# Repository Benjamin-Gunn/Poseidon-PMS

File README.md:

# Poseidon-PMS
Power Management System for Poseidon.

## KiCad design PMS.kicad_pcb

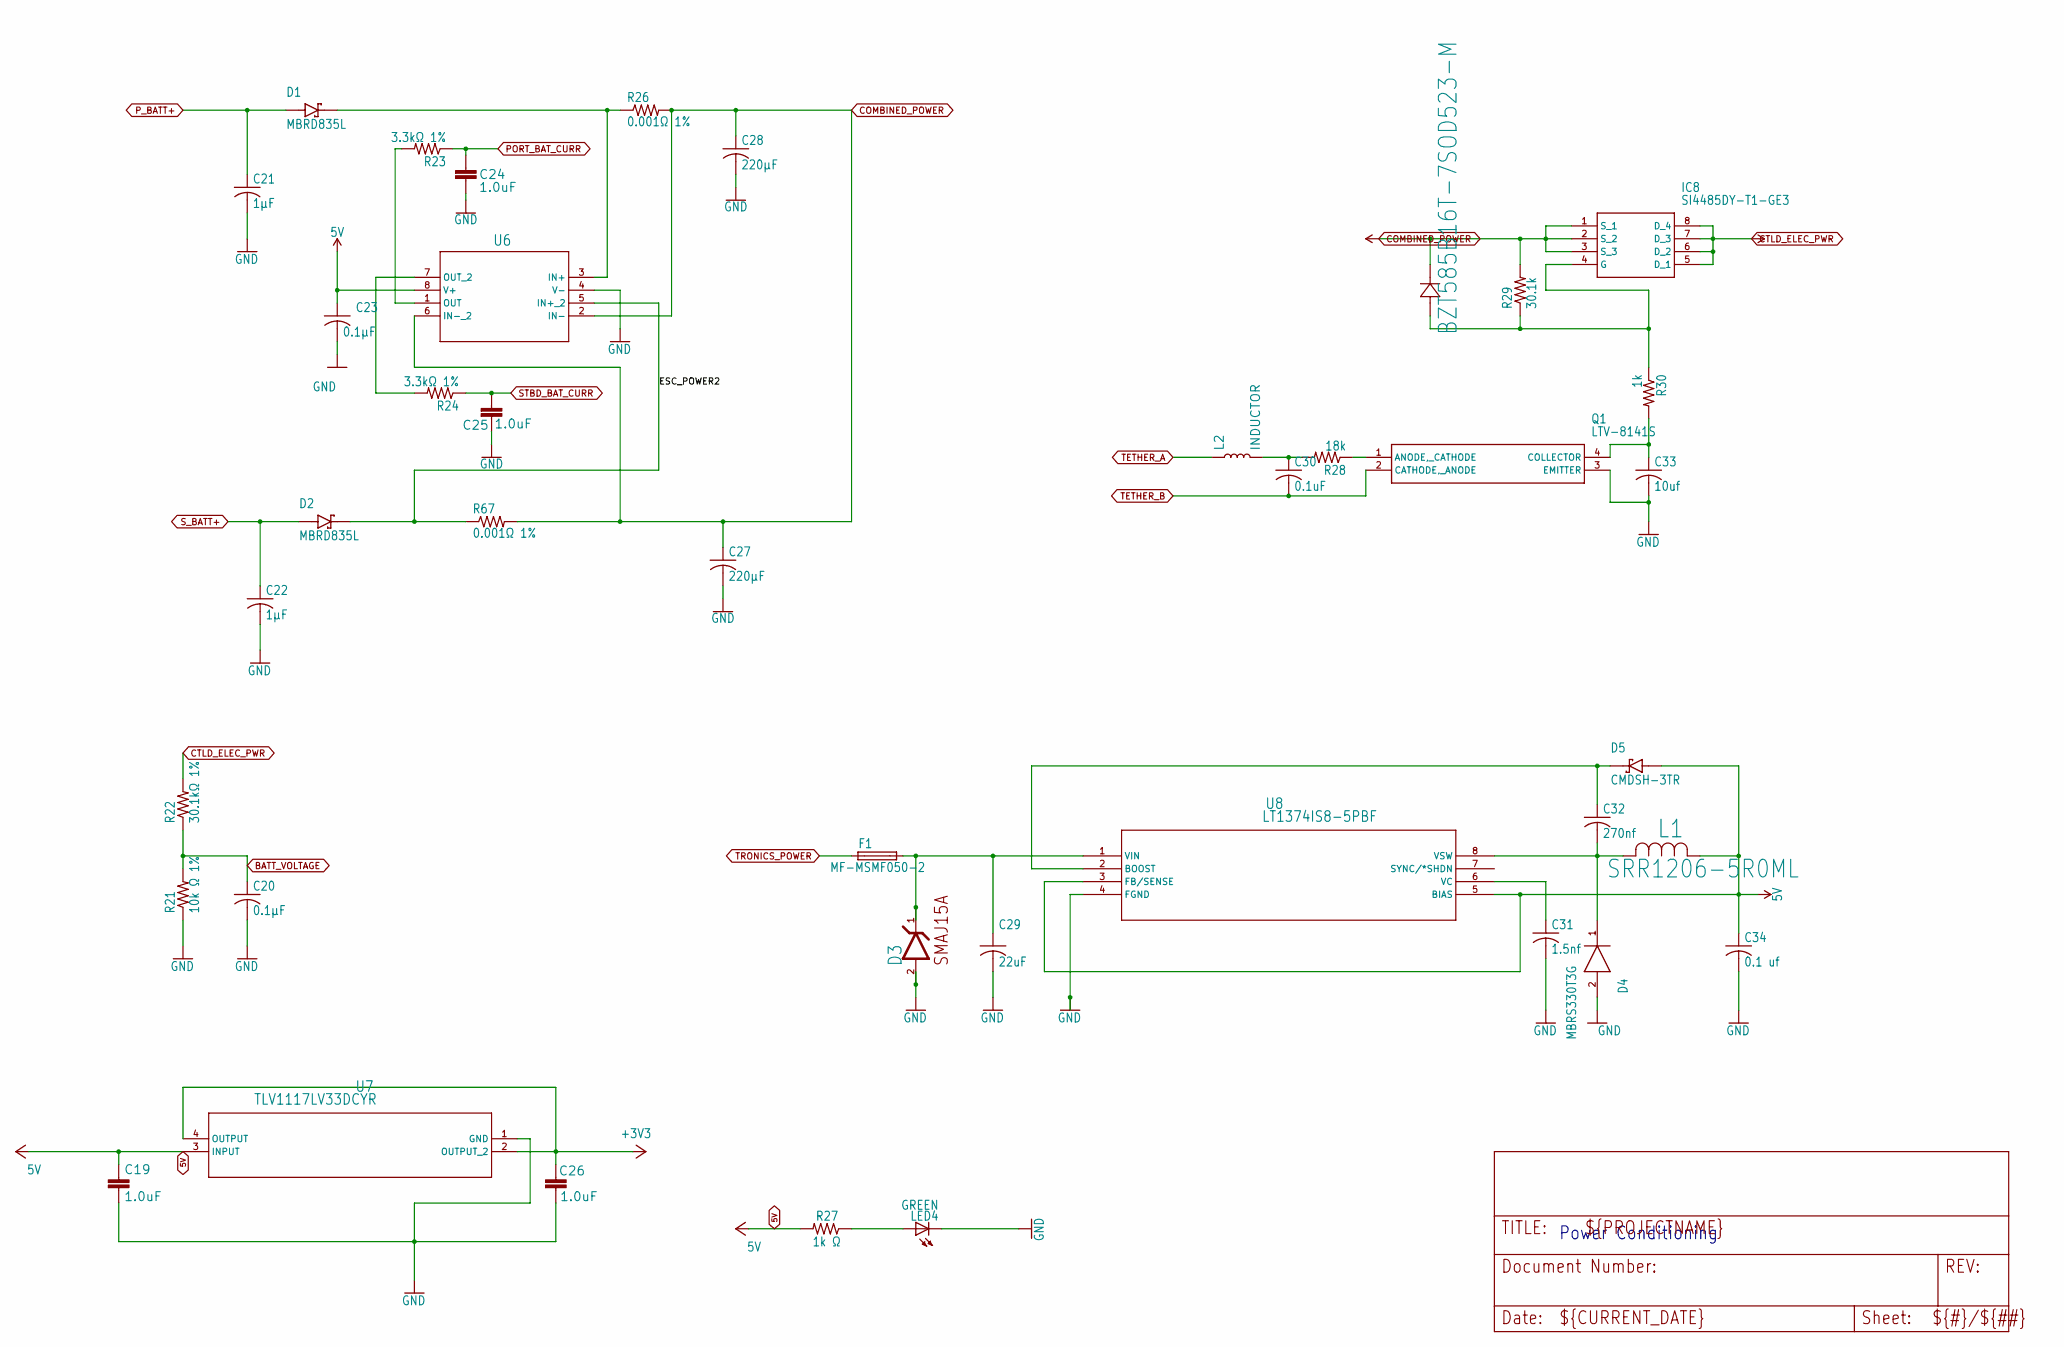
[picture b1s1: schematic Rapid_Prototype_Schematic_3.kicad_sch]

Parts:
C19, C24, C25, C26: 1.0uF; C_0805_2012Metric
C20, C23: 0.1µF; C_0805_2012Metric
C21, C22: 1µF; C_0805_2012Metric
C27, C28: 220µF; C_1206_3216Metric
C29: 22uF; C_0805_2012Metric
C30: 0.1uF; C_0805_2012Metric
C31: 1.5nf; C_0805_2012Metric
C32: 270nf; C_0805_2012Metric
C33: 10uf; C_0805_2012Metric
C34: 0.1 uf; C_0805_2012Metric
CR1: BZT585B16T-7SOD523-M; D_SOD-323_HandSoldering
D1, D2: MBRD835L; TO-252-3_TabPin2_1
D3: BOURNS-INC.---SMAJ15A_BOURNS_INC._SMAJ15ABOURNS_I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; D_SMA_Handsoldering
D4: MBRS330T3G; D_SMC_Handsoldering
D5: CMDSH-3TR; D_SOD-323_HandSoldering
F1: MF-MSMF050-2; Fuse_1812_4532Metric_Pad1.30x3.40mm_HandSolder
IC8: SI4485DY-T1-GE3; SOIC-8_3.9x4.9mm_P1.27mm
L1: SRR1206-5R0ML; IND_BOURNS_SRR1240
L2: INDUCTOR; SRP1770TA-3R3M_BRN
LED4: GREEN; LED_0805_2012Metric_Pad1.15x1.40mm_HandSolder
Q1: LTV-8141S; LTV8141STA1
R21: 10k Ω 1%; R_0805_2012Metric_Pad1.20x1.40mm_HandSolder
R22: 30.1kΩ 1%; R_0805_2012Metric_Pad1.20x1.40mm_HandSolder
R23, R24: 3.3kΩ 1%; R_0805_2012Metric_Pad1.20x1.40mm_HandSolder
R26, R67: 0.001Ω 1%; R_0805_2012Metric_Pad1.20x1.40mm_HandSolder
R27: 1k Ω; R_0805_2012Metric_Pad1.20x1.40mm_HandSolder
R28: 18k; R_0805_2012Metric_Pad1.20x1.40mm_HandSolder
R29: 30.1k; R_0805_2012Metric_Pad1.20x1.40mm_HandSolder
R30: 1k; R_0805_2012Metric_Pad1.20x1.40mm_HandSolder
U6: LM2904ITPX/NOPB; SOIC-8_3.9x4.9mm_P1.27mm
U7: TLV1117LV33DCYR; SOT-223
U8: LT1374IS8-5PBF; SOIC-8_3.9x4.9mm_P1.27mm

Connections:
5V: C19.1, C23.1, C34.1, D5.2 (A), L1.1, R27.2, U6.8 (V+), U7.3 (INPUT), U8.3 (FB/SENSE), U8.5 (BIAS); also elsewhere on the board
+3V3: C26.1, U7.2 (OUTPUT_2), U7.4 (OUTPUT); also elsewhere on the board
/Rapid_Prototype_Schematic_3/ESC_POWER2: D2.2 (K), R67.1, U6.5 (IN+_2)
BATT_VOLTAGE: C20.1, R21.2, R22.1; also elsewhere on the board
COMBINED_POWER: C27.1, C28.1, CR1.1, IC8.1 (S_1), IC8.2 (S_2), IC8.3 (S_3), R26.2, R29.2, R67.2, U6.2 (IN-), U6.6 (IN-_2); also elsewhere on the board
CTLD_ELEC_PWR: IC8.5 (D_1), IC8.6 (D_2), IC8.7 (D_3), IC8.8 (D_4), R22.2; also elsewhere on the board
GND: C19.2, C20.2, C21.2, C22.2, C23.2, C24.2, C25.2, C26.2, C27.2, C28.2, C29.2, C31.2, C33.2, C34.2, D3.2 (ANODE), D4.2 (A), LED4.1 (C), Q1.3 (EMITTER), R21.1, U6.4 (V-), U7.1 (GND), U8.4 (FGND); also elsewhere on the board
unnamed: C30.1, L2.2, R28.2
unnamed: D1.2 (K), R26.1, U6.3 (IN+)
unnamed: C29.1, D3.1 (CATHODE), F1.2, U8.1 (VIN)
unnamed: C32.2, D4.1 (K), L1.2, U8.8 (VSW)
unnamed: C32.1, D5.1 (C), U8.2 (BOOST)
unnamed: CR1.2, IC8.4 (G), R29.1, R30.1
unnamed: LED4.2 (A), R27.1
unnamed: Q1.1 (ANODE,_CATHODE), R28.1
unnamed: C33.1, Q1.4 (COLLECTOR), R30.2
unnamed: R23.2, U6.1 (OUT)
unnamed: R24.2, U6.7 (OUT_2)
unnamed: C31.1, U8.6 (VC)
PORT_BAT_CURR: C24.1, R23.1; also elsewhere on the board
P_BATT+: C21.1, D1.1 (A); also elsewhere on the board
STBD_BAT_CURR: C25.1, R24.1; also elsewhere on the board
S_BATT+: C22.1, D2.1 (A); also elsewhere on the board
TETHER_A: L2.1; also elsewhere on the board
TETHER_B: C30.2, Q1.2 (CATHODE,_ANODE); also elsewhere on the board
TRONICS_POWER: F1.1; also elsewhere on the board

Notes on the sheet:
Power Conditioning

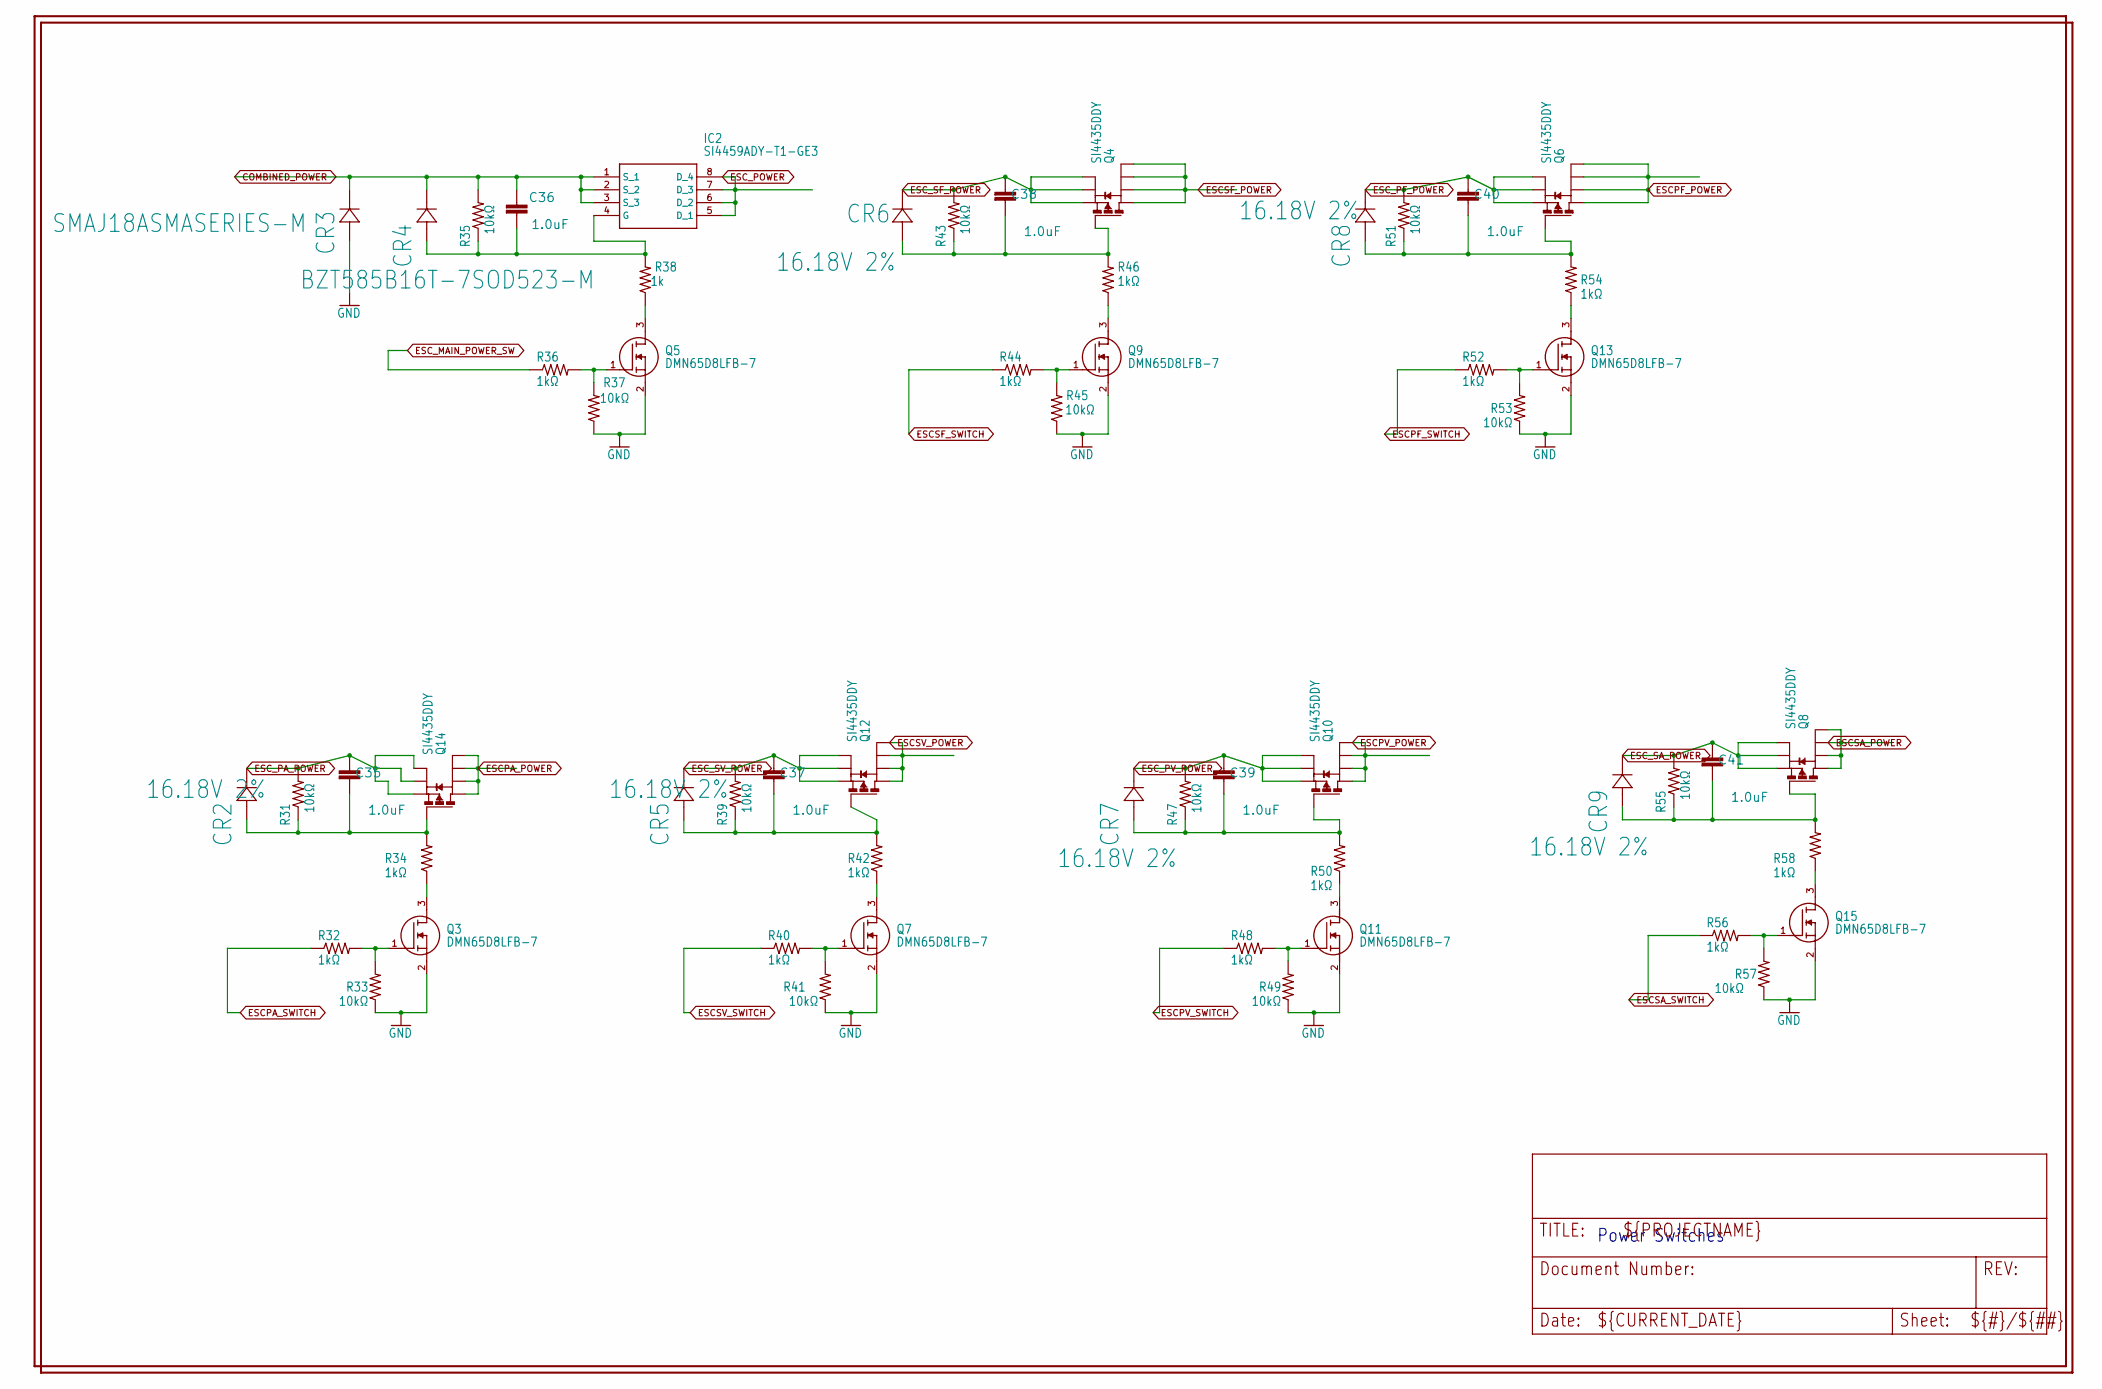
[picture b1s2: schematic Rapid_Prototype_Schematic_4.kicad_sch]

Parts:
C35, C36, C37, C38, C39, C40, C41: 1.0uF; C_0805_2012Metric
CR2, CR5, CR6, CR7, CR8, CR9: 16.18V 2%; D_SOD-323_HandSoldering
CR3: SMAJ18ASMASERIES-M; D_SMA_Handsoldering
CR4: BZT585B16T-7SOD523-M; D_SOD-323_HandSoldering
IC2: SI4459ADY-T1-GE3; SOIC-8_3.9x4.9mm_P1.27mm
Q3, Q5, Q7, Q9, Q11, Q13, Q15: DMN65D8LFB-7; SOT-23-3
Q4, Q6, Q8, Q10, Q12, Q14: SI4435DDY; SOIC-8_3.9x4.9mm_P1.27mm
R31, R33, R35, R37, R39, R41, R43, R45, R47, R49, R51, R53, R55, R57: 10kΩ; R_0805_2012Metric_Pad1.20x1.40mm_HandSolder
R32, R34, R36, R40, R42, R44, R46, R48, R50, R52, R54, R56, R58: 1kΩ; R_0805_2012Metric_Pad1.20x1.40mm_HandSolder
R38: 1k; R_0805_2012Metric_Pad1.20x1.40mm_HandSolder

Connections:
COMBINED_POWER: C36.1, CR3.1, CR4.1, IC2.1 (S_1), IC2.2 (S_2), IC2.3 (S_3), R35.2; also elsewhere on the board
ESCPA_POWER: Q14.5 (D@1), Q14.6 (D@2), Q14.7 (D@3), Q14.8 (D@4); also elsewhere on the board
ESCPA_SWITCH: R32.1; also elsewhere on the board
ESCPF_POWER: Q6.5 (D@1), Q6.6 (D@2), Q6.7 (D@3), Q6.8 (D@4); also elsewhere on the board
ESCPF_SWITCH: R52.1; also elsewhere on the board
ESCPV_POWER: Q10.5 (D@1), Q10.6 (D@2), Q10.7 (D@3), Q10.8 (D@4); also elsewhere on the board
ESCPV_SWITCH: R48.1; also elsewhere on the board
ESCSA_POWER: Q8.5 (D@1), Q8.6 (D@2), Q8.7 (D@3), Q8.8 (D@4); also elsewhere on the board
ESCSA_SWITCH: R56.1; also elsewhere on the board
ESCSF_POWER: Q4.5 (D@1), Q4.6 (D@2), Q4.7 (D@3), Q4.8 (D@4); also elsewhere on the board
ESCSF_SWITCH: R44.1; also elsewhere on the board
ESCSV_POWER: Q12.5 (D@1), Q12.6 (D@2), Q12.7 (D@3), Q12.8 (D@4); also elsewhere on the board
ESCSV_SWITCH: R40.1; also elsewhere on the board
ESC_MAIN_POWER_SW: R36.1; also elsewhere on the board
ESC_PA_POWER: C35.1, CR2.1, Q14.1 (S@1), Q14.2 (S@2), Q14.3 (S@3), R31.2; also elsewhere on the board
ESC_PF_POWER: C40.1, CR8.1, Q6.1 (S@1), Q6.2 (S@2), Q6.3 (S@3), R51.2; also elsewhere on the board
ESC_POWER: IC2.5 (D_1), IC2.6 (D_2), IC2.7 (D_3), IC2.8 (D_4); also elsewhere on the board
ESC_PV_POWER: C39.1, CR7.1, Q10.1 (S@1), Q10.2 (S@2), Q10.3 (S@3), R47.2; also elsewhere on the board
ESC_SA_POWER: C41.1, CR9.1, Q8.1 (S@1), Q8.2 (S@2), Q8.3 (S@3), R55.2; also elsewhere on the board
ESC_SF_POWER: C38.1, CR6.1, Q4.1 (S@1), Q4.2 (S@2), Q4.3 (S@3), R43.2; also elsewhere on the board
ESC_SV_POWER: C37.1, CR5.1, Q12.1 (S@1), Q12.2 (S@2), Q12.3 (S@3), R39.2; also elsewhere on the board
GND: CR3.2, Q3.2 (S), Q5.2 (S), Q7.2 (S), Q9.2 (S), Q11.2 (S), Q13.2 (S), Q15.2 (S), R33.1, R37.1, R41.1, R45.1, R49.1, R53.1, R57.1; also elsewhere on the board
unnamed: C36.2, CR4.2, IC2.4 (G), R35.1, R38.2
unnamed: Q3.3 (D), R34.1
unnamed: Q3.1 (G), R32.2, R33.2
unnamed: C38.2, CR6.2, Q4.4 (G), R43.1, R46.2
unnamed: Q5.3 (D), R38.1
unnamed: Q5.1 (G), R36.2, R37.2
unnamed: C40.2, CR8.2, Q6.4 (G), R51.1, R54.2
unnamed: Q7.3 (D), R42.1
unnamed: Q7.1 (G), R40.2, R41.2
unnamed: C41.2, CR9.2, Q8.4 (G), R55.1, R58.2
unnamed: Q9.3 (D), R46.1
unnamed: Q9.1 (G), R44.2, R45.2
unnamed: C39.2, CR7.2, Q10.4 (G), R47.1, R50.2
unnamed: Q11.3 (D), R50.1
unnamed: Q11.1 (G), R48.2, R49.2
unnamed: C37.2, CR5.2, Q12.4 (G), R39.1, R42.2
unnamed: Q13.3 (D), R54.1
unnamed: Q13.1 (G), R52.2, R53.2
unnamed: C35.2, CR2.2, Q14.4 (G), R31.1, R34.2
unnamed: Q15.3 (D), R58.1
unnamed: Q15.1 (G), R56.2, R57.2

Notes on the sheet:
Power Switches

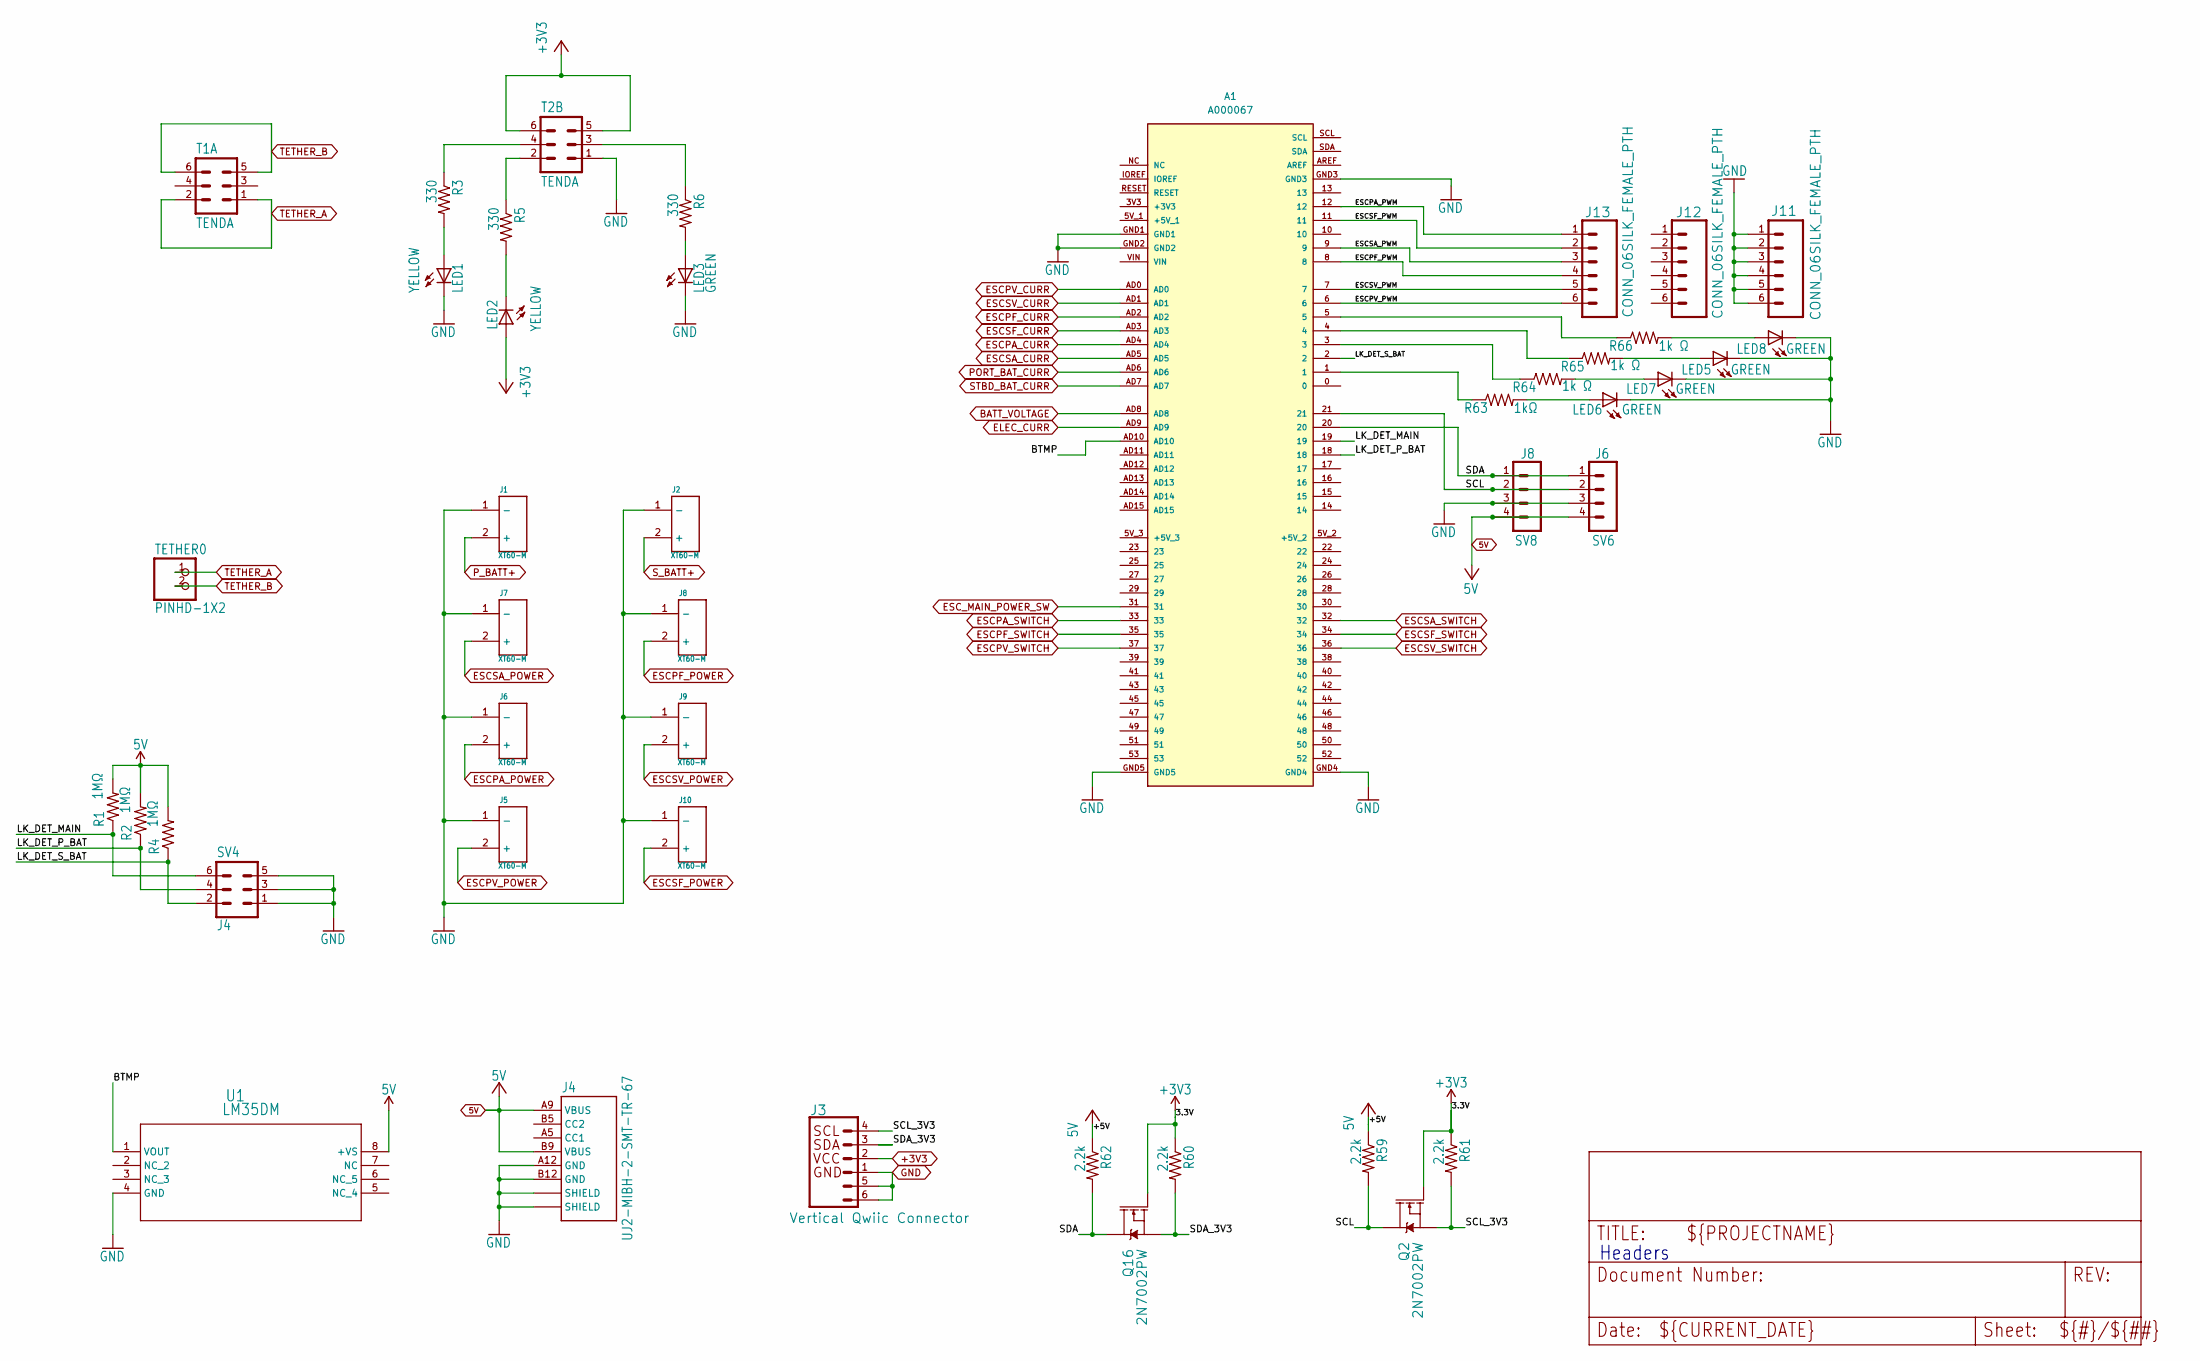
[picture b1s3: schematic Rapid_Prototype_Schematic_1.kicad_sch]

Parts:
A1: A000067; MODULE_A000067
J1, J2, J5, J6, J7, J8, J9, J10: XT60-M; AMASS_XT60-M_1x02_P7.20mm_Vertical
J3: Vertical Qwiic Connector; CONN_BM04B-SRSS-TB_SPK
J4: UJ2-MIBH-2-SMT-TR-67; GCT_USB4125-GF-A_REVA2
J11, J12, J13: CONN_06SILK_FEMALE_PTH; PinSocket_1x06_P2.54mm_Vertical
LED1, LED2: YELLOW; LED_0805_2012Metric_Pad1.15x1.40mm_HandSolder
LED3, LED5, LED6, LED7, LED8: GREEN; LED_0805_2012Metric_Pad1.15x1.40mm_HandSolder
Q2, Q16: 2N7002PW; SOT-23-3
R1, R2, R4: 1MΩ; R_0805_2012Metric_Pad1.20x1.40mm_HandSolder
R3, R5, R6: 330; R_0805_2012Metric_Pad1.20x1.40mm_HandSolder
R59, R60, R61, R62: 2.2k; R_0805_2012Metric_Pad1.20x1.40mm_HandSolder
R63: 1kΩ; R_0805_2012Metric_Pad1.20x1.40mm_HandSolder
R64, R65, R66: 1k Ω; R_0805_2012Metric_Pad1.20x1.40mm_HandSolder
SV4: J4; PinSocket_2x03_P2.54mm_Vertical
SV6: J6; PinSocket_1x04_P2.54mm_Vertical
SV8: J8; PinSocket_1x04_P2.54mm_Vertical
T1, T2: TENDA; PinSocket_2x03_P2.54mm_Vertical
TETHER0: PINHD-1X2; PinSocket_1x02_P2.54mm_Vertical
U1: LM35DM; SOIC-8_3.9x4.9mm_P1.27mm

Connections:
5V: J4.A9 (VBUS), J4.B9 (VBUS), R1.2, R2.2, R4.2, R59.1, R62.1, SV6.4, SV8.4, U1.8 (+VS); also elsewhere on the board
+3V3: J3.2, LED2.2 (A), Q2.1 (G), Q16.1 (G), R60.1, R61.1, T2.5, T2.6; also elsewhere on the board
/Rapid_Prototype_Schematic_1/BTMP: A1.AD10, U1.1 (VOUT)
/Rapid_Prototype_Schematic_1/ESCPA_PWM: A1.12, J13.1
/Rapid_Prototype_Schematic_1/ESCPF_PWM: A1.8, J13.4
/Rapid_Prototype_Schematic_1/ESCPV_PWM: A1.6, J13.6
/Rapid_Prototype_Schematic_1/ESCSA_PWM: A1.9, J13.3
/Rapid_Prototype_Schematic_1/ESCSF_PWM: A1.11, J13.2
/Rapid_Prototype_Schematic_1/ESCSV_PWM: A1.7, J13.5
/Rapid_Prototype_Schematic_1/LK_DET_MAIN: A1.19, R1.1, SV4.6
/Rapid_Prototype_Schematic_1/LK_DET_P_BAT: A1.18, R2.1, SV4.4
/Rapid_Prototype_Schematic_1/LK_DET_S_BAT: A1.2, R4.1, SV4.2
/Rapid_Prototype_Schematic_1/SCL: A1.21, Q2.3 (D), R59.2, SV6.2, SV8.2
/Rapid_Prototype_Schematic_1/SCL_3V3: J3.4, Q2.2 (S), R61.2
/Rapid_Prototype_Schematic_1/SDA: A1.20, Q16.3 (D), R62.2, SV6.1, SV8.1
/Rapid_Prototype_Schematic_1/SDA_3V3: J3.3, Q16.2 (S), R60.2
BATT_VOLTAGE: A1.AD8; also elsewhere on the board
ELEC_CURR: A1.AD9; also elsewhere on the board
ESCPA_CURR: A1.AD4; also elsewhere on the board
ESCPA_POWER: J6.2 (+); also elsewhere on the board
ESCPA_SWITCH: A1.33; also elsewhere on the board
ESCPF_CURR: A1.AD2; also elsewhere on the board
ESCPF_POWER: J8.2 (+); also elsewhere on the board
ESCPF_SWITCH: A1.35; also elsewhere on the board
ESCPV_CURR: A1.AD0; also elsewhere on the board
ESCPV_POWER: J5.2 (+); also elsewhere on the board
ESCPV_SWITCH: A1.37; also elsewhere on the board
ESCSA_CURR: A1.AD5; also elsewhere on the board
ESCSA_POWER: J7.2 (+); also elsewhere on the board
ESCSA_SWITCH: A1.32; also elsewhere on the board
ESCSF_CURR: A1.AD3; also elsewhere on the board
ESCSF_POWER: J10.2 (+); also elsewhere on the board
ESCSF_SWITCH: A1.34; also elsewhere on the board
ESCSV_CURR: A1.AD1; also elsewhere on the board
ESCSV_POWER: J9.2 (+); also elsewhere on the board
ESCSV_SWITCH: A1.36; also elsewhere on the board
ESC_MAIN_POWER_SW: A1.31; also elsewhere on the board
GND: A1.GND1, A1.GND2, A1.GND3, A1.GND4, A1.GND5, J1.1 (-), J2.1 (-), J3.1, J3.5 (GND), J3.6 (GND), J4.A12 (GND), J4.B12 (GND), J4.S1 (SHIELD), J4.S2 (SHIELD), J4.S3 (SHIELD), J4.S4 (SHIELD), J5.1 (-), J6.1 (-), J7.1 (-), J8.1 (-), J9.1 (-), J10.1 (-), J11.1, J11.2, J11.3, J11.4, J11.5, J11.6, LED1.1 (C), LED3.1 (C), LED5.1 (C), LED6.1 (C), LED7.1 (C), LED8.1 (C), SV4.1, SV4.3, SV4.5, SV6.3, SV8.3, T2.1, U1.4 (GND); also elsewhere on the board
unnamed: A1.1, R63.1
unnamed: A1.3, R64.1
unnamed: A1.4, R65.1
unnamed: A1.5, R66.1
unnamed: LED1.2 (A), R3.2
unnamed: LED2.1 (C), R5.2
unnamed: LED3.2 (A), R6.2
unnamed: LED5.2 (A), R65.2
unnamed: LED6.2 (A), R63.2
unnamed: LED7.2 (A), R64.2
unnamed: LED8.2 (A), R66.2
unnamed: R3.1, T2.4
unnamed: R5.1, T2.2
unnamed: R6.1, T2.3
PORT_BAT_CURR: A1.AD6; also elsewhere on the board
P_BATT+: J1.2 (+); also elsewhere on the board
STBD_BAT_CURR: A1.AD7; also elsewhere on the board
S_BATT+: J2.2 (+); also elsewhere on the board
TETHER_A: T1.1, T1.2, TETHER0.1; also elsewhere on the board
TETHER_B: T1.5, T1.6, TETHER0.2; also elsewhere on the board

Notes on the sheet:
Headers

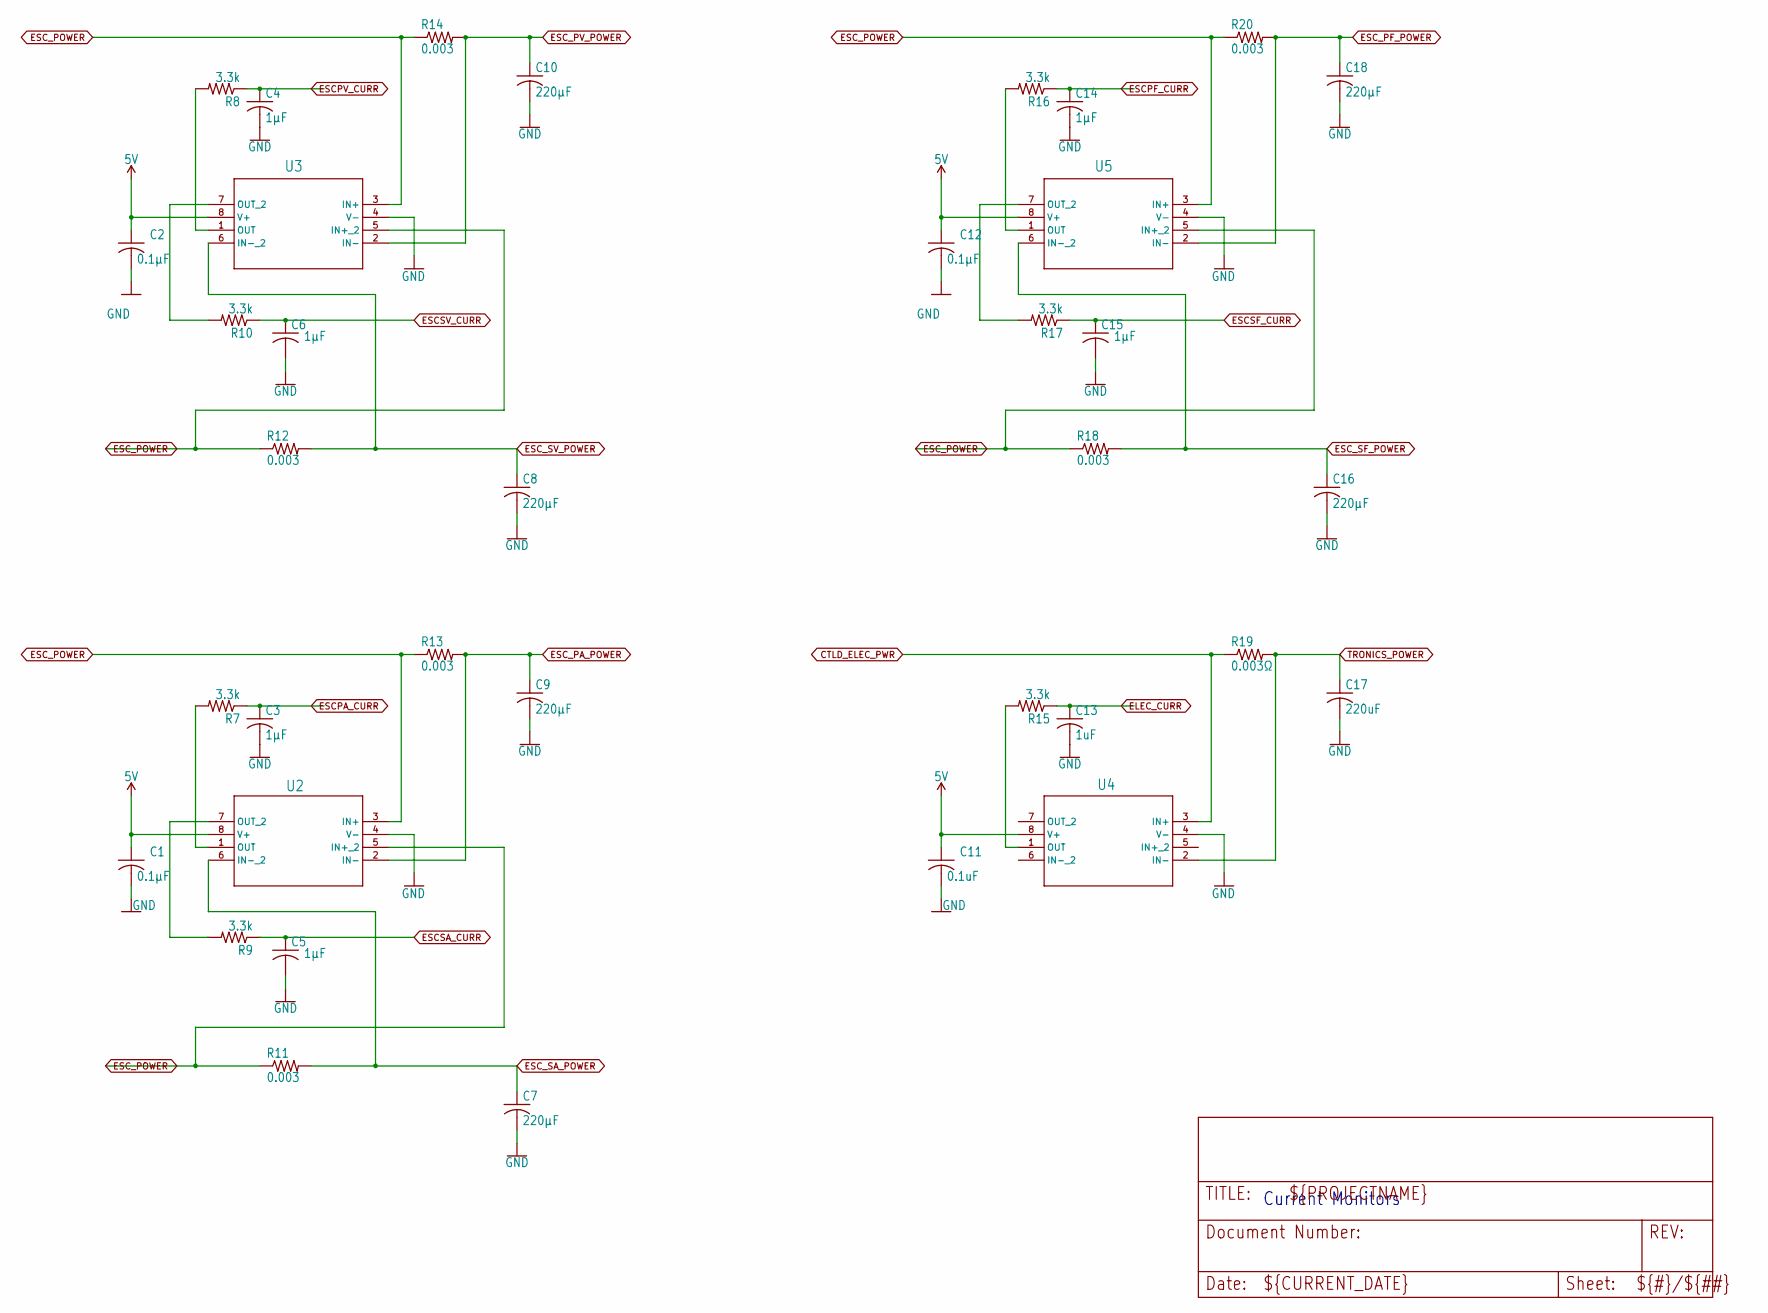
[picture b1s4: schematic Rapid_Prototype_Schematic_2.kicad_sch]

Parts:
C1, C2, C12: 0.1µF; C_0805_2012Metric
C3, C4, C5, C6, C14, C15: 1µF; C_0805_2012Metric
C7, C8, C9, C10, C16, C18: 220µF; C_1206_3216Metric
C11: 0.1uF; C_0805_2012Metric
C13: 1uF; C_0805_2012Metric
C17: 220uF; C_1206_3216Metric
R7, R8, R9, R10, R15, R16, R17: 3.3k; R_0805_2012Metric_Pad1.20x1.40mm_HandSolder
R11, R12, R13, R14, R18, R20: 0.003; R_0805_2012Metric_Pad1.20x1.40mm_HandSolder
R19: 0.003Ω; R_0805_2012Metric_Pad1.20x1.40mm_HandSolder
U2, U3, U4, U5: LM2904ITPX/NOPB; SOIC-8_3.9x4.9mm_P1.27mm

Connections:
5V: C1.1, C2.1, C11.1, C12.1, U2.8 (V+), U3.8 (V+), U4.8 (V+), U5.8 (V+); also elsewhere on the board
CTLD_ELEC_PWR: R19.1, U4.3 (IN+); also elsewhere on the board
ELEC_CURR: C13.1, R15.1; also elsewhere on the board
ESCPA_CURR: C3.1, R7.1; also elsewhere on the board
ESCPF_CURR: C14.1, R16.1; also elsewhere on the board
ESCPV_CURR: C4.1, R8.1; also elsewhere on the board
ESCSA_CURR: C5.1, R9.1; also elsewhere on the board
ESCSF_CURR: C15.1, R17.1; also elsewhere on the board
ESCSV_CURR: C6.1, R10.1; also elsewhere on the board
ESC_PA_POWER: C9.1, R13.2, U2.2 (IN-); also elsewhere on the board
ESC_PF_POWER: C18.1, R20.2, U5.2 (IN-); also elsewhere on the board
ESC_POWER: R11.1, R12.1, R13.1, R14.1, R18.1, R20.1, U2.3 (IN+), U2.5 (IN+_2), U3.3 (IN+), U3.5 (IN+_2), U5.3 (IN+), U5.5 (IN+_2); also elsewhere on the board
ESC_PV_POWER: C10.1, R14.2, U3.2 (IN-); also elsewhere on the board
ESC_SA_POWER: C7.1, R11.2, U2.6 (IN-_2); also elsewhere on the board
ESC_SF_POWER: C16.1, R18.2, U5.6 (IN-_2); also elsewhere on the board
ESC_SV_POWER: C8.1, R12.2, U3.6 (IN-_2); also elsewhere on the board
GND: C1.2, C2.2, C3.2, C4.2, C5.2, C6.2, C7.2, C8.2, C9.2, C10.2, C11.2, C12.2, C13.2, C14.2, C15.2, C16.2, C17.2, C18.2, U2.4 (V-), U3.4 (V-), U4.4 (V-), U5.4 (V-); also elsewhere on the board
unnamed: R7.2, U2.1 (OUT)
unnamed: R9.2, U2.7 (OUT_2)
unnamed: R8.2, U3.1 (OUT)
unnamed: R10.2, U3.7 (OUT_2)
unnamed: R15.2, U4.1 (OUT)
unnamed: R16.2, U5.1 (OUT)
unnamed: R17.2, U5.7 (OUT_2)
TRONICS_POWER: C17.1, R19.2, U4.2 (IN-); also elsewhere on the board

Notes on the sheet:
Current Monitors

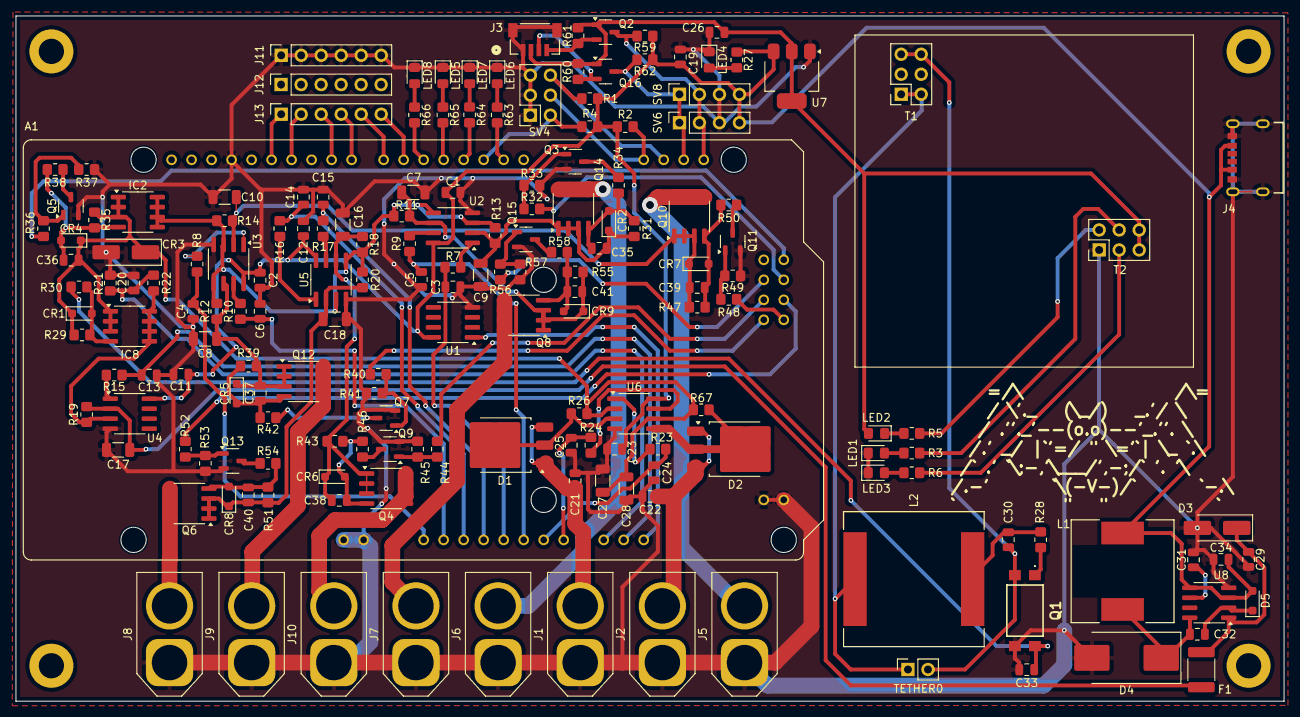
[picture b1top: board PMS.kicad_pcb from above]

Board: 2 copper layers, 161.0 x 87.0 mm, 178 parts (0 on the bottom side), 109 nets.

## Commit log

2025-04-10 Initial Commit
    Here's everything!
2025-04-10 Add Mounting Holes
2025-04-30 PMS refresh
2025-04-30 Fixed Library Dependancies
2025-05-01 PMS V2 Arrangement
2025-05-01 PMS Slim
2025-05-22 Backup Restored
2025-05-28 Update Visual w/ PMS Slim
